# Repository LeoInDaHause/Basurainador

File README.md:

# Integrantes
Cesar Leonardo Rodriguez León

Diego Fernando Carvajal Lagos

Jhohan Stiven Rodriguez Rodriguez

# BASURA-INADOR

Este proyecto que tiene como objetivo central crear una cultura positiva alrededor de las basuras, en esto se trata sobre el reciclaje y el manejo de las basuras. con el objetivo de lograr esto se crea un "artefacto" que sea didactico y que llame la atención de niños entre los 5 a 7 años.

Para lograr construir este proyecto "artefacto", se a realizado una investigación previa, alrededor de la cultura y de como contruir esta cultura en los niños. y tambien se realizo una investigación sobre los materiales para usar, y de la manera mas eficiente de conseguir este artefacto.

las concluciones obtenidas de estas investigaciones son:

1. Por parte de lo cultural, se identificó que la mejor manera de crear una cultura en los niños eran son estímulos que a estos les llamara la atención, por ejemplo luces y sonidos.

2. A partir de la investigación realizada para temas de material y eficiencia del proyecto, de decide el uso de un microcontrolador, junto a un sensor de color, luces led, y sonidos.

En un principio se tenia la idea de realizar 3 canecas de basura que tubieran el objetivo de separar las basuras, en organicos, papel y carton, y metales y vidrios. A medida que fue avanzando el tiempo el proyecto cada vez era mas pulido. hasta el punto en el que unicamente se utilizaria una caneca, y a partir de esto, mediante una pantalla(lcd o oled), se le pidiera al usuario ingresear un tipo de basura, mediante un sensor (TCS3200) detectaria el color de la basura y determinaria, mediante un programa desde el microcontrolador (ESP32), si este elemento es el solicitado o no. en caso de que el elemento fuera correcto, este arrojaria la LUZ del elemento y produciria un sonido "positivo", y habriria la tapa de la caneca, en caso contrario este arrojaria una LUZ diferente al elemento y produciria un sonido "malo", y la tapa no habriría.

De esta manera se espera que el niño de 5 a 7 años interactue con el "artefacto" sin aburrirse, y genernado en este la cultura deseada, para solucionar una problematica que se vive en la actualidad y que tiene graves consecuencias, como lo es el impacto a la salud, clima, biodiversidad, suciedad, entre otras cosas.

Las teorias que sustentan este proyecto son fisicas orientadas a la elecctronica, y sociales orientadas a la cultura.

## Teorias orientadas a la electrónica:
1. Leyes de Ohm
2. Leyes de Kirchhoff
3. Leyes de Maxwell
4. Teoria de telecomunicaciones
5. Teoria del control

## Teoria orientadas a la cultura:
1. Teoria del juego
2. Condicionamiento Clasico
3. Condicionamiento Operante
4. Teoría de la actividad de Elkonin

# Diagrama de Flujo:

# Diagrama de Caja negra:

# Diagrama de Tecnológico:

# Póster:

# Proyecto Finalizado:

(video)

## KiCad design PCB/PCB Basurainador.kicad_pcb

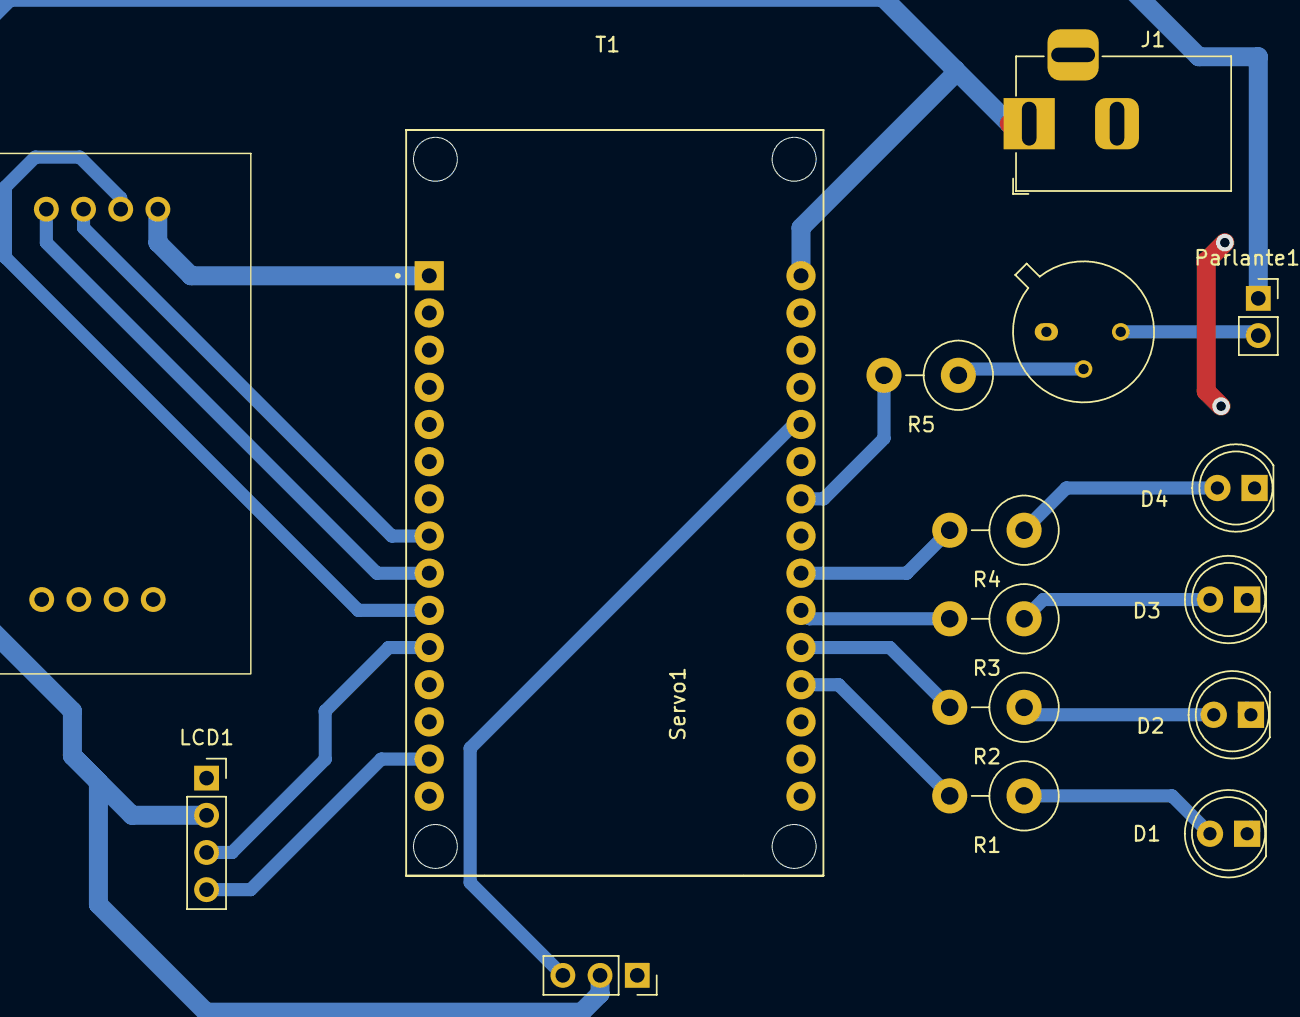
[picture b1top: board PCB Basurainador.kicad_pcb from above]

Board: 2 copper layers, 16 parts (0 on the bottom side), 18 nets.

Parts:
D1, D2, D3, D4: LED; LED_D5.0mm
J1: Barrel Jack; BarrelJack_Horizontal
LCD1: Conn_01x04_Socket; PinSocket_1x04_P2.54mm_Vertical
Parlante1: Conn_01x02_Socket; PinSocket_1x02_P2.54mm_Vertical
R1, R2, R3, R4, R5: R; R_Axial_DIN0414_L11.9mm_D4.5mm_P5.08mm_Vertical
Servo1: Conn_01x03_Socket; PinSocket_1x03_P2.54mm_Vertical
T1: 2N2222A; TO-39-3
U1: ESP32-DEVKIT-V1; MODULE_ESP32_DEVKIT_V1
U2: TCS3200; SOIC127P600X175-8N

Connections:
+3V3: U1.1 (3V3), U2.8 (S3)
+5V: J1.1, LCD1.2, Parlante1.1, Servo1.2, U1.30 (VIN)
/D5: U1.8 (D5), U2.6 (OUT)
/D14: Servo1.3, U1.26 (D14)
/D18: U1.9 (D18), U2.5 (VDD)
/D19: U1.10 (D19), U2.7 (S2)
/D21: LCD1.3, U1.11 (D21)
/D22: LCD1.4, U1.14 (D22)
/D32: R4.2, U1.22 (D33)
/D33: R3.2, U1.21 (D32)
/D34: R2.2, U1.20 (D35)
/D35: R1.2, U1.19 (D34)
/P1: Parlante1.2, T1.3 (C)
GND: D1.1 (K), D2.1 (K), D3.1 (K), D4.1 (K), J1.2, J1.3, LCD1.1, Servo1.1, T1.1 (E), U1.2 (GND), U1.29 (GND), U2.4 (GND)
unnamed: D1.2 (A), R1.1
unnamed: D2.2 (A), R2.1
unnamed: D3.2 (A), R3.1
unnamed: D4.2 (A), R4.1

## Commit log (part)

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2023-11-14 Create sensor TCS3200
2023-11-14 Create ESP32
2023-11-18 Create Proceso de Planeación
2023-11-18 Create A
2023-11-18 Create videos
2023-11-18 Create Codigos ESP32
2023-11-18 Rename planificacion del proyecto.md to Planificacion del proyecto.md
2023-11-19 Rename Rasbperry Pi Pico to Rasbperry.md
2023-11-19 Rename ESP32.md to Esp32.md
2023-11-19 Rename Programacion.md to Programacion
2023-11-19 Update Programacion
2023-11-19 Rename Programacion to Codigo General
2023-11-19 Update Codigo General
2023-11-19 Rename Librerias.md to Librerias
2023-11-23 Create Sensor TC3200
2023-11-30 Create Diseño implementación software
2023-11-30 Create wefws
2023-11-30 Rename cbcb.txt to Diagrama(s) de flujo.txt
2023-12-01 git push
